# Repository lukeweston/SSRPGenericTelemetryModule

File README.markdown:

- Micro-SD card for removable datalogging and storage   
- Real-time clock with battery backup   
- USB interface for battery recharging as well as PC-based communications, programming, debugging or data analysis   
- Barometric pressure sensor (30,000 feet approx. maximum)   
- 3-axis MEMS gyroscope   
- 3-axis accelerometer   
- 3-axis magnetometer   
- Single-axis high-range accelerometer (up to 200 g-units) for rocket motor characterisation   
- Differential pressre transducer for pitot tube airspeed measurement   
- Temperature sensor   
- Central microcontroller (Atmel ATmega2561)   
- On-board Silicon Labs Si1000 microcontroller with integrated UHF transceiver (100mW transmit power)   
- Power supply from a single 3.7V lithium-polymer cell, with on-board recharge control   
- 8 channels of 0-4096mV analog data acquisition from additional external payload electronics.   
- Support for a range of different GPS receiver modules and different antenna types, mounted away from the main board to provide more flexible antenna mounting.   
- Support for a range of different external RF telemetry hardware if more performance is desired than the on-board Si1000 can provide.   
- For example, the RFDesign RFD900 900 MHz RF modem can be used, which consists of a Si1000 microcontroller with external RF LNA and PA, providing telemetry ranges of up to
nearly 100 kilometers with line-of-sight.

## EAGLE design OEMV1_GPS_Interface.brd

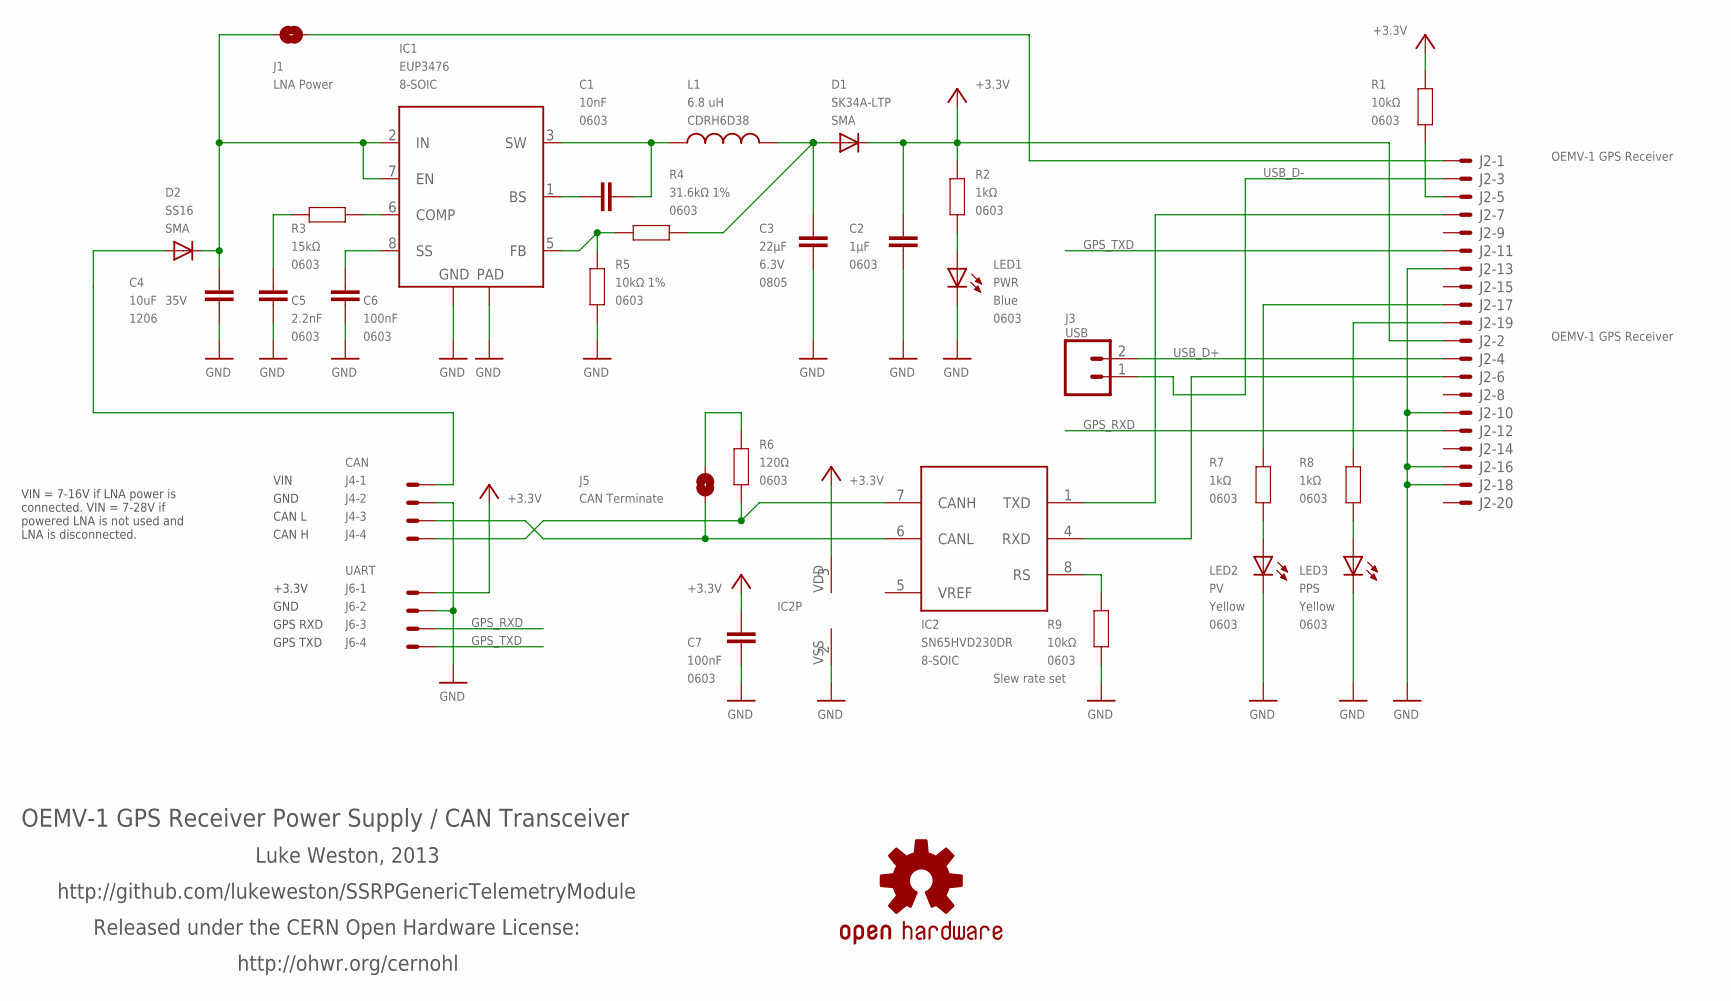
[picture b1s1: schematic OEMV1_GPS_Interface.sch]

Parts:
C1: 10nF; 0603
C2: 1µF; 0603
C3: 22µF; 0805; VOLTAGE 6.3V
C4: 10uF; C1206; VOLTAGE 35V
C5: 2.2nF; 0603
C6, C7: 100nF; 0603
D1: SK34A-LTP; SMA-DIODE
D2: SS16; SMA-DIODE
IC1: EUP3476; SO08T
IC2: SN65HVD230DR; SO-08
J1: LNA Power; SJ
J2: OEMV-1 GPS Receiver; 87758-2016
J3: USB; 1X02
J4: CAN; 22-23-2041
J5: CAN Terminate; SJ
J6: UART; 22-23-2041
L1: 6.8 uH; CDRH
LED1: PWR; LED-0603
LED2: PV; LED-0603
LED3: PPS; LED-0603
R1, R9: 10kΩ; 0603
R2, R7, R8: 1kΩ; 0603
R3: 15kΩ; 0603
R4: 31.6kΩ 1%; 0603
R5: 10kΩ 1%; 0603
R6: 120Ω; 0603
SY: OSHW-LOGOS; OSHW-LOGO-S

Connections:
!RESET: J2.5, R1.2
+3.3V: C2.2, C7.2, D1.C, IC2.3 (VDD), J2.2, J6.1, R1.1, R2.1
CANH: IC2.7 (CANH), J4.4, R6.1
CANL: IC2.6 (CANL), J4.3, J5.2
GND: C2.1, C3.2, C4.2, C5.1, C6.1, C7.1, IC1.4 (GND), IC1.9 (TGND), IC2.2 (VSS), J2.10, J2.13, J2.16, J2.18, J4.2, J6.2, LED1.C, LED2.C, LED3.C, R5.2, R9.2
GPS_CAN_RX: IC2.4 (RXD), J2.6
GPS_CAN_TX: IC2.1 (TXD), J2.7
GPS_RXD: J2.12, J6.3
GPS_TXD: J2.11, J6.4
unnamed: LED2.A, R7.1
unnamed: LED3.A, R8.1
unnamed: C1.2, IC1.1 (BS)
unnamed: D2.A, J4.1
unnamed: J5.1, R6.2
unnamed: C5.2, R3.2
unnamed: C3.1, D1.A, L1.2, R4.2
unnamed: LED1.A, R2.2
unnamed: C4.1, D2.C, IC1.2 (IN), IC1.7 (EN), J1.1
unnamed: C1.1, IC1.3 (SW), L1.1
unnamed: IC1.6 (COMP), R3.1
unnamed: C6.2, IC1.8 (SS)
unnamed: IC1.5 (FB), R4.1, R5.1
unnamed: IC2.8 (RS), R9.1
PPS_OUT: J2.19, R8.2
PV_OUT: J2.17, R7.2
USB_D+: J2.4, J3.2
USB_D-: J2.3, J3.1
VIN: J1.2, J2.1
VREF: IC2.5 (VREF)

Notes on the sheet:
OEMV-1 GPS Receiver Power Supply / CAN Transceiver
Luke Weston, 2013
http://github.com/lukeweston/SSRPGenericTelemetryModule
Released under the CERN Open Hardware License:
http://ohwr.org/cernohl
VIN
GND
CAN L
CAN H
+3.3V
GPS RXD
GPS TXD
VIN = 7-16V if LNA power is connected. VIN = 7-28V if powered LNA is not used and LNA is disconnected.

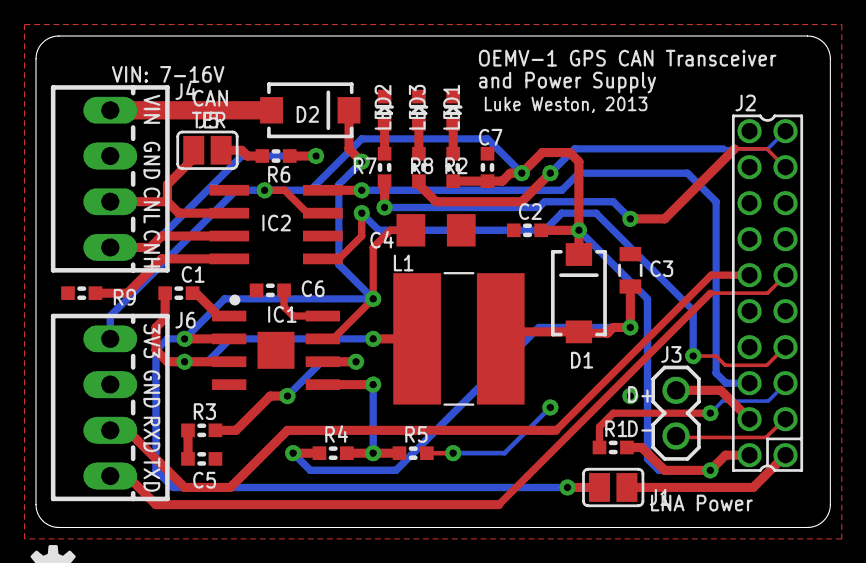
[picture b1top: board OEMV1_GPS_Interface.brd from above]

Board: 2 copper layers, 44.1 x 27.3 mm, 31 parts (0 on the bottom side), 28 nets.

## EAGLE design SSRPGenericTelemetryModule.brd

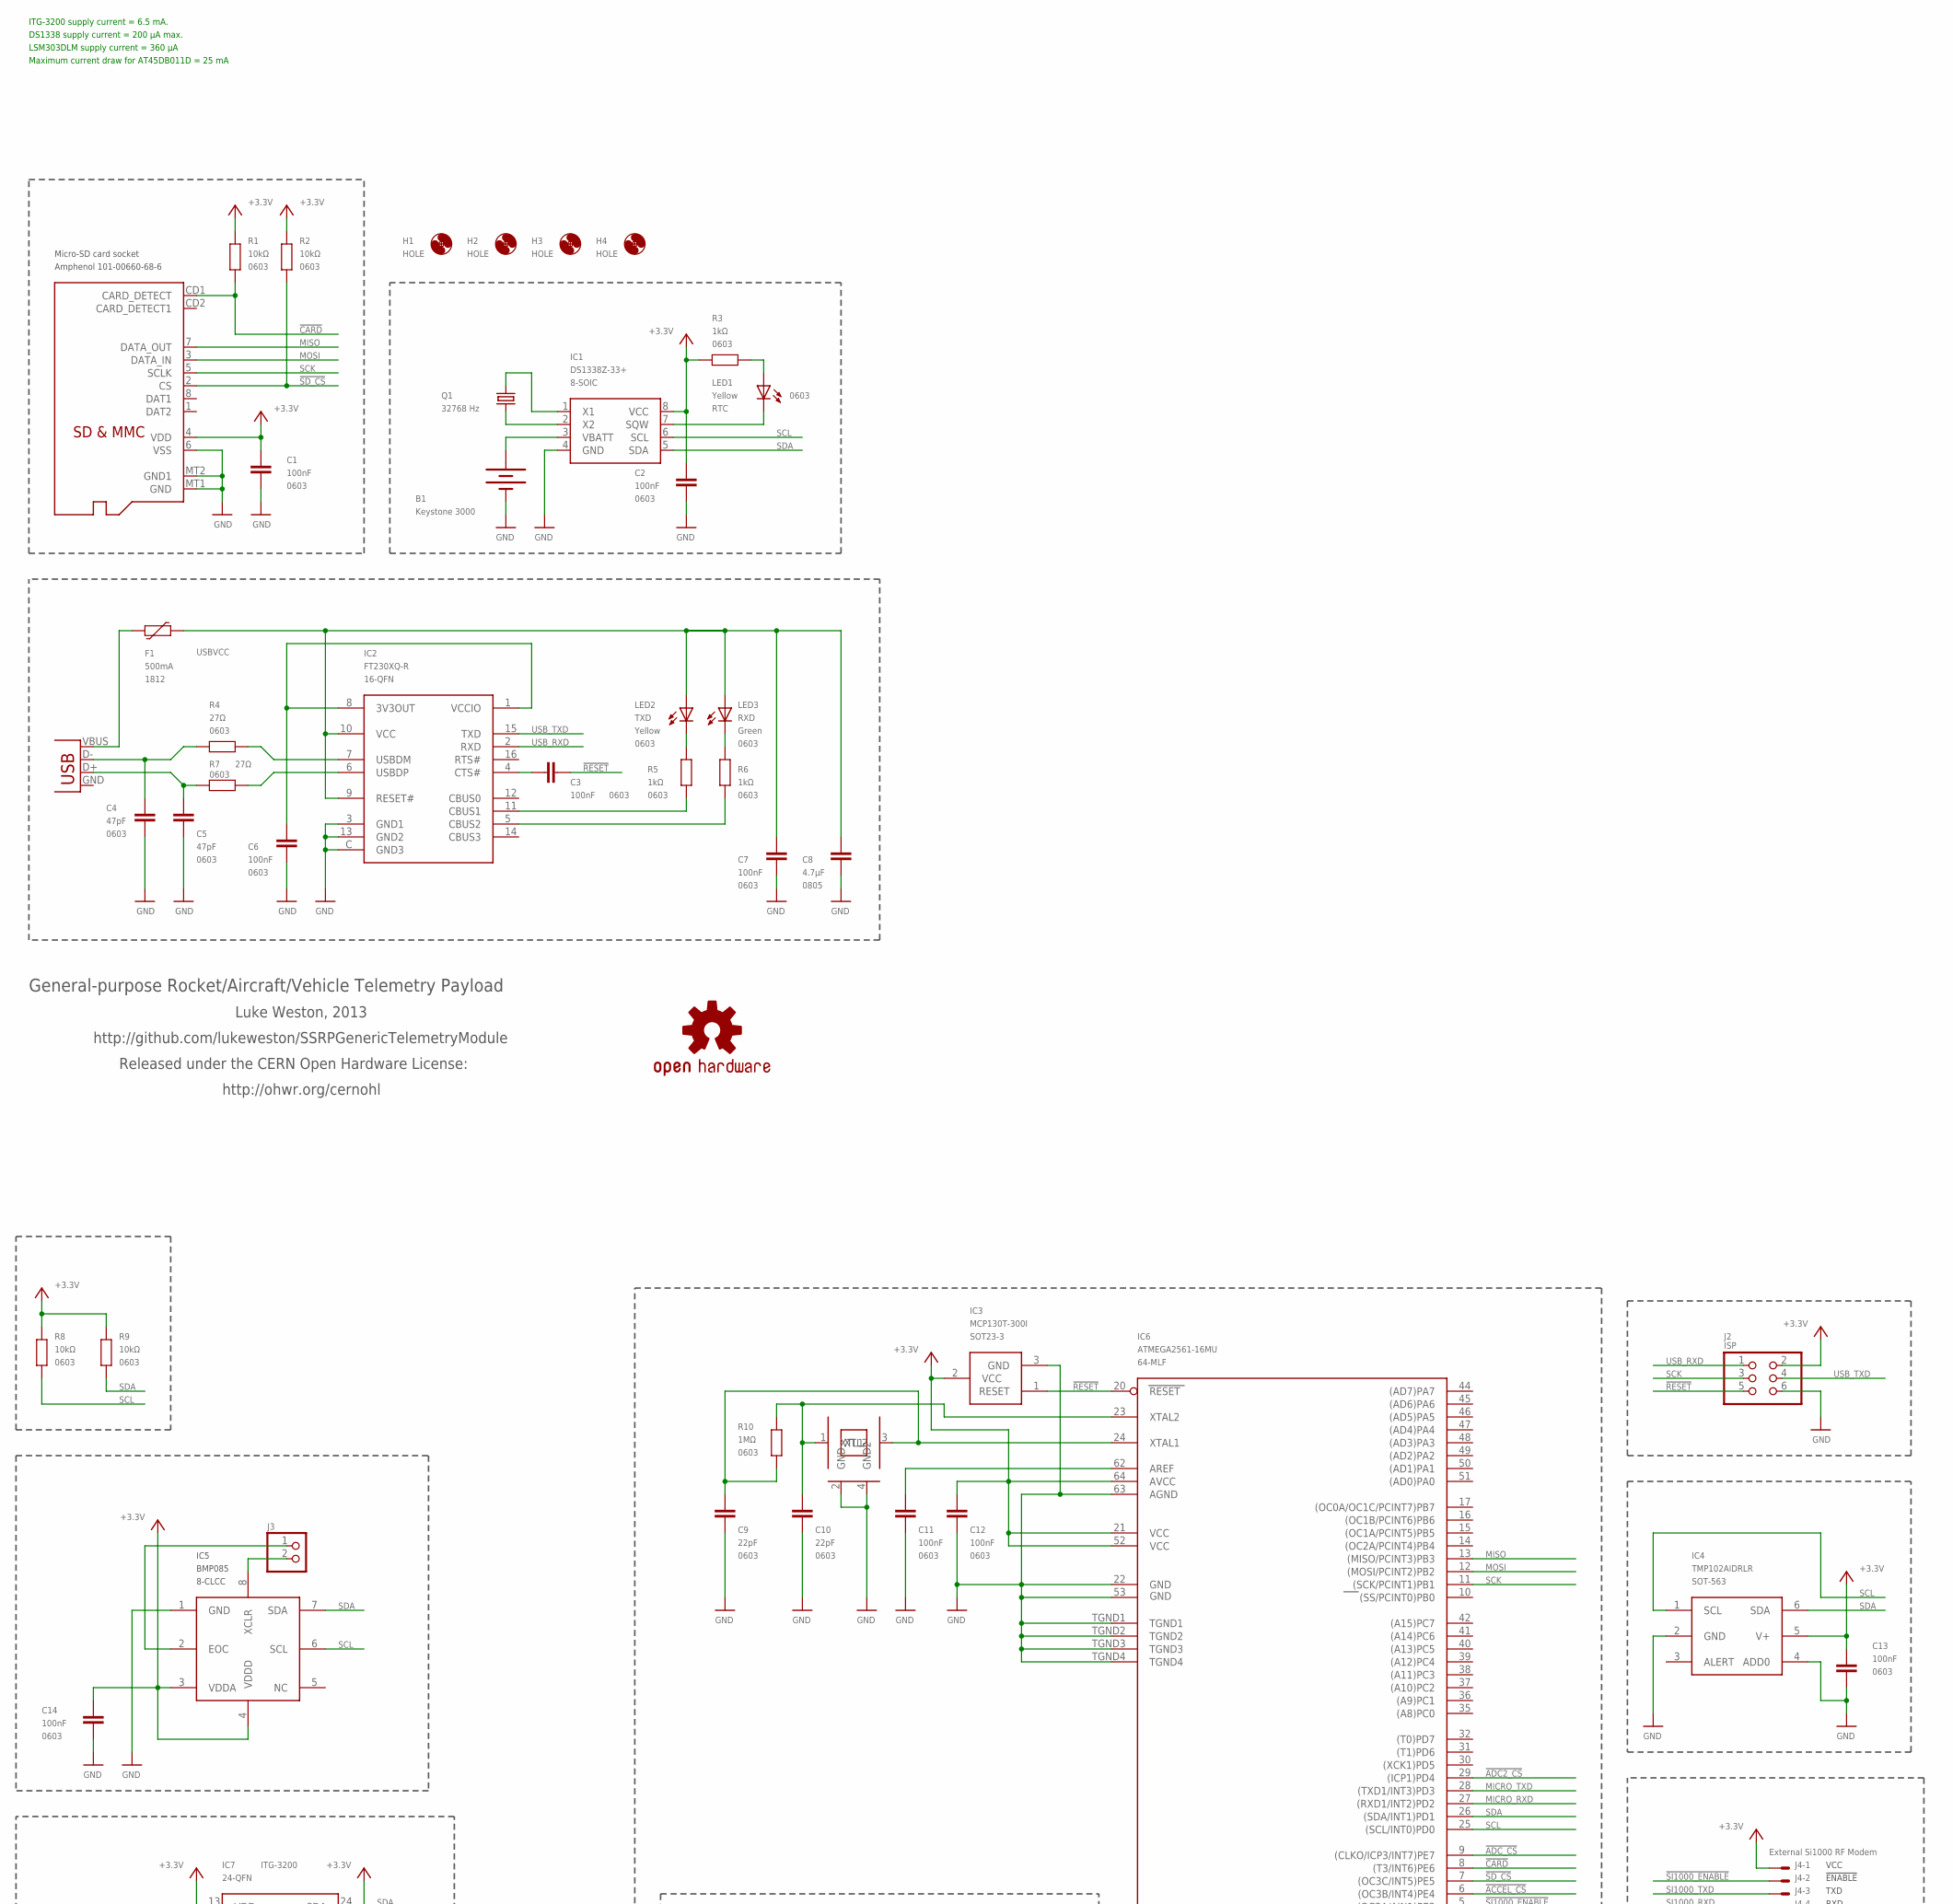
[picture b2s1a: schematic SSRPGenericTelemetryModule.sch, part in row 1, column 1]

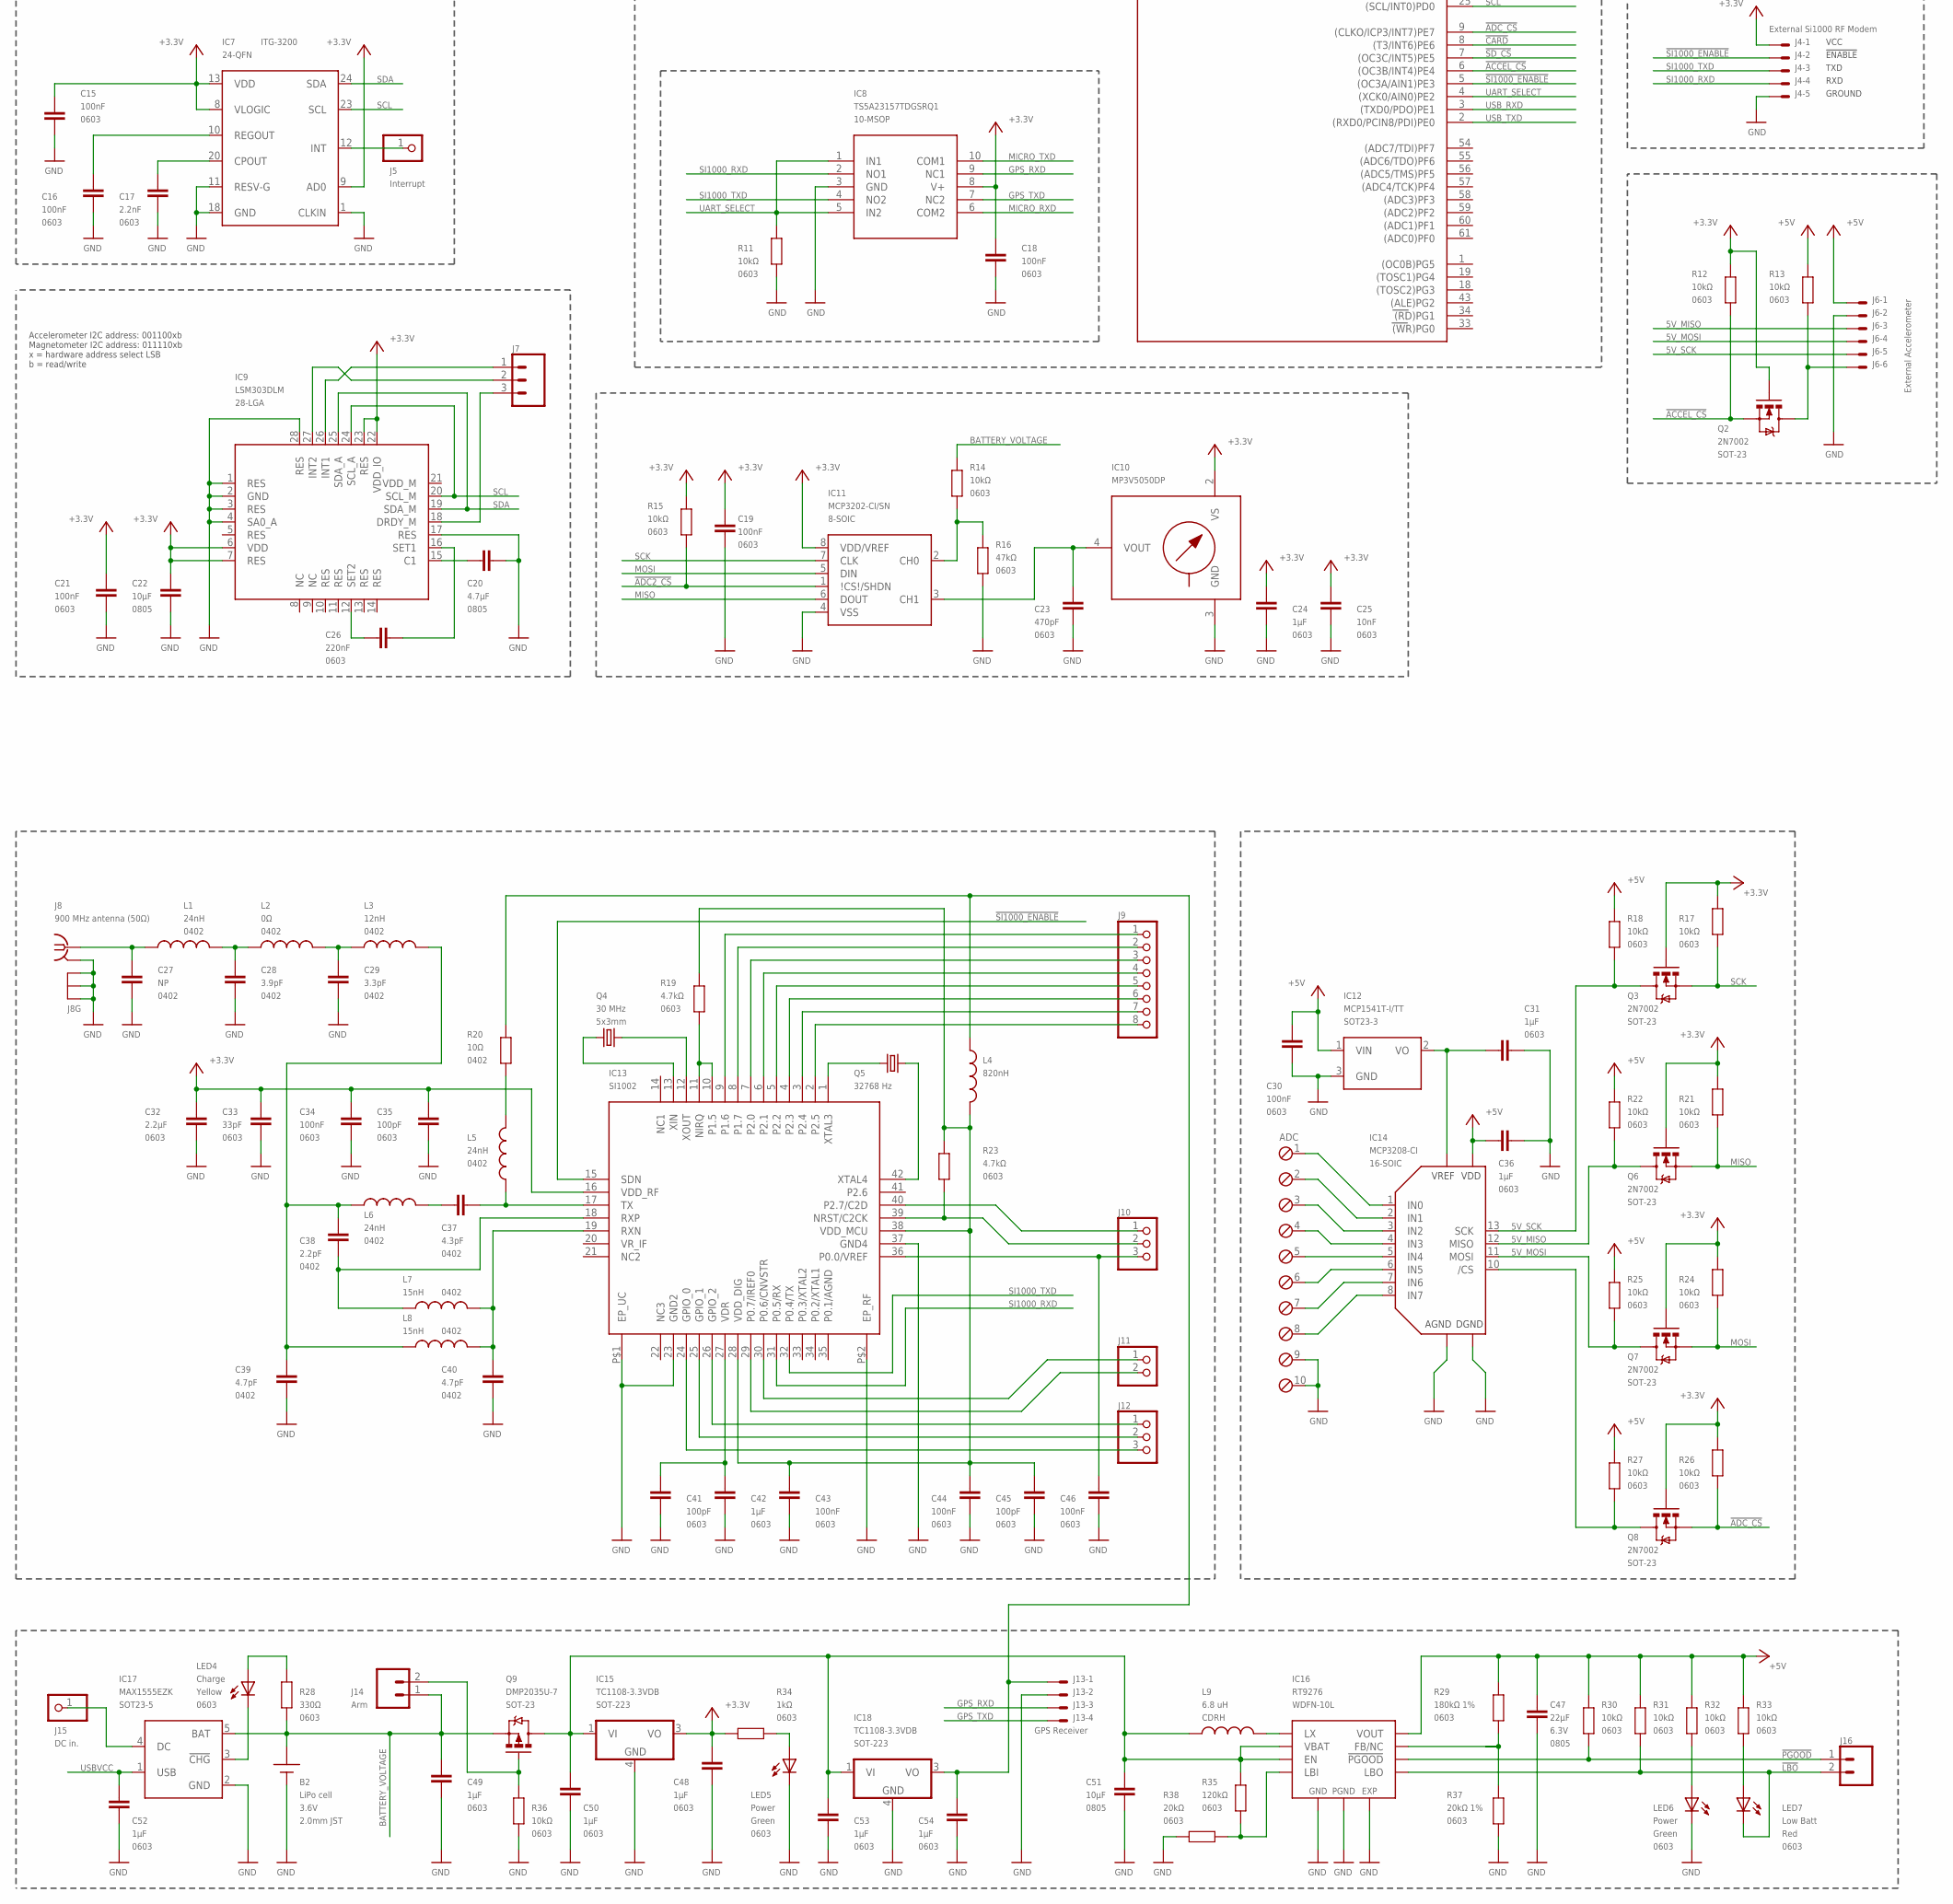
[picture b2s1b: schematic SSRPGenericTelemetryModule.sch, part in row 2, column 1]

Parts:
B1: Keystone 3000; BATTCON_12MM
B2: LiPo cell; JST-2MM-TH-RA; VOLTAGE 3.6V
C1, C2, C3, C6, C7, C11, C12, C13, C14, C15, C16, C18, C19, C21, C30, C34, C43, C44, C46: 100nF; 0603
C4, C5: 47pF; 0603
C8, C20: 4.7µF; 0805
C9, C10: 22pF; 0603
C17: 2.2nF; 0603
C22, C51: 10µF; 0805
C23: 470pF; 0603
C24, C31, C36, C42, C48, C49, C50, C52, C53, C54: 1µF; 0603
C25: 10nF; 0603
C26: 220nF; 0603
C27: NP; C0402
C28: 3.9pF; C0402
C29: 3.3pF; C0402
C32: 2.2µF; 0603
C33: 33pF; 0603
C35, C41, C45: 100pF; 0603
C37: 4.3pF; C0402
C38: 2.2pF; C0402
C39, C40: 4.7pF; C0402
C47: 22µF; 0805; VOLTAGE 6.3V
F1: 500mA; 1812
H1, H2, H3, H4: HOLE; 3,2
IC1: DS1338Z-33+; SO08@1
IC2: FT230XQ-R; QFN4X4-16
IC3: MCP130T-300I; SOT23-3
IC4: TMP102AIDRLR; SOT563
IC5: BMP085
IC6: ATMEGA2561-16MU; MLF64
IC7: ITG-3200; QFN-24
IC8: TS5A23157TDGSRQ1; MSOP10
IC9: LSM303DLM; LGA28-5X5
IC10: MP3V5050DP; 1351
IC11: MCP3202-CI/SN; SO-08
IC12: MCP1541T-I/TT; SOT23
IC13: SI1002; QFN42_MCM
IC14: MCP3208-CI; SOIC16
IC15, IC18: TC1108-3.3VDB; SOT223
IC16: RT9276; WDFN-10L-3X3
IC17: MAX1555EZK; SOT23-5L
J1: MicroSD Card; ADAFRUIT_MICROSD
J2: ISP; 2X03PTH
J3, J11: PINHD-1X2; 1X02
J4: External Si1000 RF Modem; 22-23-2051
J5: Interrupt; 1X01
J6: External Accelerometer; 7395-06
J7: M03PTH; 1X03
J8: 900 MHz antenna (50Ω); J502-ND-142-0701-801/806
J9: PINHD-1X8; 1X08
J10, J12: PINHD-1X3; 1X03
J13: GPS Receiver; 7395-04
J14: Arm; 1X02
J15: DC in.; 1X01
J16: Status; 1X02
L1, L5, L6: 24nH; C0402
L2: 0Ω; C0402
L3: 12nH; C0402
L4: 820nH; C0402
L7, L8: 15nH; C0402
L9: 6.8 uH; CDRH
LED1: RTC; LED-0603
LED2: TXD; LED-0603
LED3: RXD; LED-0603
LED4: Charge; LED-0603
LED5, LED6: Power; LED-0603
LED7: Low Batt; LED-0603
Q1, Q5: 32768 Hz; SMD3215_XTAL
Q2, Q3, Q6, Q7, Q8: 2N7002; SOT23-3
Q4: 30 MHz; CRYSTAL-SMD-5X3
Q9: DMP2035U-7; SOT23-3
R1, R2, R8, R9, R11, R12, R13, R14, R15, R17, R18, R21, R22, R24, R25, R26, R27, R30, R31, R32, R33, R36: 10kΩ; 0603
R3, R5, R6, R34: 1kΩ; 0603
R4, R7: 27Ω; 0603
R10: 1MΩ; 0603
R16: 47kΩ; 0603
R19, R23: 4.7kΩ; 0603
R20: 10Ω; C0402
R28: 330Ω; 0603
R29: 180kΩ 1%; 0603
R35: 120kΩ; 0603
R37: 20kΩ 1%; 0603
R38: 20kΩ; 0603
SY: OSHW-LOGOS; OSHW-LOGO-S
X1: USB-MICROB
X2: ADC; 10POL254
XTL1: SMD3225-16MHZ 3.2 x 2.5mm crystal; CRYSTAL-SMD-3X2

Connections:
5V_MISO: IC14.12 (MISO), J6.3, Q6.3 (D), R22.1
5V_MOSI: IC14.11 (MOSI), J6.4, Q7.3 (D), R25.1
5V_SCK: IC14.13 (SCK), J6.5, Q3.3 (D), R18.1
!ACCEL_CS: IC6.6 ((OC3B/INT4)PE4), Q2.2 (S), R12.1
!ADC2_CS: IC6.29 ((ICP1)PD4), IC11.1 (\!CS\!/SHDN), R15.1
!ADC_CS: IC6.9 ((CLKO/ICP3/INT7)PE7), Q8.2 (S), R26.1
!ADC_CS_5V: IC14.10 (/CS), Q8.3 (D), R27.1
!CARD: IC6.8 ((T3/INT6)PE6), J1.CD1 (CARD_DETECT), R1.2
!LBO: IC16.4 (LBO), J16.2, LED7.C, R31.1
!PGOOD: IC16.8 (!PGOOD), J16.1, R30.1
!RESET: C3.2, IC3.1 (RESET), IC6.20 (RESET), J2.5
!SD_CS: IC6.7 ((OC3C/INT5)PE5), J1.2 (CS), R2.2
!SI1000_ENABLE: IC6.5 ((OC3A/AIN1)PE3), IC13.15 (SDN), J4.2
+3V3: C1.1, C2.1, C12.1, C13.1, C14.1, C15.1, C18.2, C19.1, C21.2, C22.2, C24.1, C25.1, C32.2, C33.2, C34.2, C35.2, C48.1, IC1.8 (VCC), IC3.2 (VCC), IC4.5 (V+), IC5.3 (VDDA), IC5.4 (VDDD), IC6.21 (VCC), IC6.52 (VCC1), IC6.64 (AVCC), IC7.8 (VLOGIC), IC7.9 (AD0), IC7.13 (VDD), IC8.8 (V+), IC9.6 (VDD), IC9.7 (RES), IC9.22 (VDD_IO), IC9.23 (RES), IC10.2 (VS), IC11.8 (VDD/VREF), IC13.16 (VDD_RF), IC15.3 (VO), J1.4 (VDD), J2.2, J4.1, Q2.1 (G), Q3.1 (G), Q6.1 (G), Q7.1 (G), Q8.1 (G), R1.1, R2.1, R3.2, R8.2, R9.2, R12.2, R15.2, R17.2, R21.2, R24.2, R26.2, R34.2
+5V: C30.2, C36.1, C47.1, IC12.1 (VIN), IC14.16 (VDD), IC16.2 (VOUT), J6.1, R13.2, R18.2, R22.2, R25.2, R27.2, R29.2, R30.2, R31.2, R32.2, R33.2
ANALOG_BAROMETER: C23.1, IC10.4 (VOUT), IC11.3 (CH1)
BATTERY_VOLTAGE: B2.+, C49.1, IC17.5 (BAT), J14.1, Q9.2 (S), R14.2, R28.1
FB1: IC16.3 (FB/NC), R29.1, R37.2
GND: B1.GND (-), B2.-, C1.2, C2.2, C4.2, C5.2, C6.2, C7.2, C8.2, C9.2, C10.2, C11.2, C12.2, C13.2, C14.2, C15.2, C16.2, C17.2, C18.1, C19.2, C20.2, C21.1, C22.1, C23.2, C24.2, C25.2, C27.2, C28.2, C29.2, C30.1, C31.2, C32.1, C33.1, C34.1, C35.1, C36.2, C39.2, C40.2, C41.1, C42.1, C43.1, C44.1, C45.1, C46.1, C47.2, C48.2, C49.2, C50.2, C51.2, C52.2, C53.2, C54.2, IC1.4 (GND), IC2.3 (GND1), IC2.13 (GND2), IC2.C (GND3), IC3.3 (GND), IC4.2 (GND), IC4.4 (ADD0), IC5.1 (GND), IC6.22 (GND), IC6.53 (GND1), IC6.63 (AGND), IC6.TGND1, IC6.TGND2, IC6.TGND3, IC6.TGND4, IC7.1 (CLKIN), IC7.11 (RESV-G), IC7.18 (GND), IC8.3 (GND), IC9.1 (RES), IC9.2 (GND), IC9.3 (RES), IC9.4 (SA0_A), IC9.17 (RES), IC9.28 (RES), IC10.3 (GND), IC11.4 (VSS), IC12.3 (GND), IC13.23 (GND2), IC13.37 (GND4), IC13.EP1 (GND5), IC13.EP2 (GND6), IC13.EP3 (GND7), IC13.EP4 (GND8), IC13.EP5 (GND9), IC13.EP6 (GND10), IC13.EP7 (GND11), IC13.EP8 (GND12), IC13.P$1 (EP_UC), IC13.P$2 (EP_RF), IC14.9 (DGND), IC14.14 (AGND), IC15.4 (GND), IC16.5 (GND), IC16.10 (PGND), IC16.EXP, IC17.2 (GND), IC18.4 (GND), J1.6 (VSS), J1.MT1 (GND), J1.MT2 (GND1), J2.6, J4.5, J6.2, J8.G@1 (GND), J8.G@2 (GND), J8.G@3 (GND), J8.G@4 (GND), J13.2, LED5.C, LED6.C, R11.1, R16.1, R36.1, R37.1, R38.1, X2.9, X2.10, XTL1.2 (GND), XTL1.4 (GND2)
GPS_RXD: IC8.9 (NC1), J13.3
GPS_TXD: IC8.7 (NC2), J13.4
LBI1: IC16.7 (LBI), R35.1, R38.2
LX1: IC16.9 (LX), L9.2
MICRO_RXD: IC6.27 ((RXD1/INT2)PD2), IC8.6 (COM2)
MICRO_TXD: IC6.28 ((TXD1/INT3)PD3), IC8.10 (COM1)
MISO: IC6.13 ((MISO/PCINT3)PB3), IC11.6 (DOUT), J1.7 (DATA_OUT), Q6.2 (S), R21.1
MOSI: IC6.12 ((MOSI/PCINT2)PB2), IC11.5 (DIN), J1.3 (DATA_IN), Q7.2 (S), R24.1
unnamed: J6.6, Q2.3 (D), R13.1
unnamed: C43.2, C44.2, C45.2, IC13.28 (VDD_DIG), IC13.38 (VDD_MCU), L4.1, R19.2, R23.2
unnamed: C38.2, IC13.18 (RXP), L7.2
unnamed: IC13.40 (P2.7/C2D), J10.1
unnamed: IC9.18 (DRDY_M), J7.3
unnamed: C27.1, J8.1, L1.1
unnamed: IC13.1 (XTAL3), Q5.X2 (2)
unnamed: IC13.42 (XTAL4), Q5.X1 (1)
unnamed: IC13.30 (P0.6/CNVSTR), J11.1
unnamed: IC9.27 (INT2), J7.2
unnamed: C11.1, IC6.62 (AREF)
unnamed: IC1.2 (X2), Q1.X2 (2)
unnamed: B1.PWR@1 (+), IC1.3 (VBATT)
unnamed: IC1.1 (X1), Q1.X1 (1)
unnamed: IC1.7 (SQW), LED1.C
unnamed: IC9.26 (INT1), J7.1
unnamed: C26.1, IC9.12 (SET2)
unnamed: C26.2, IC9.16 (SET1)
unnamed: C10.1, IC6.23 (XTAL2), R10.1, XTL1.1 (XTL1)
unnamed: C20.1, IC9.15 (C1)
unnamed: IC13.29 (P0.7/IREF0), J11.2
unnamed: IC7.12 (INT), J5.1
unnamed: C9.1, IC6.24 (XTAL1), R10.2, XTL1.3 (XTL2)
unnamed: LED1.A, R3.1
unnamed: C16.1, IC7.10 (REGOUT)
unnamed: LED2.C, R5.2
unnamed: C17.1, IC7.20 (CPOUT)
unnamed: C54.1, IC18.3 (VO), J13.1, L4.2, R20.2
unnamed: IC14.8 (IN7), X2.8
unnamed: IC14.7 (IN6), X2.7
unnamed: LED3.C, R6.2
unnamed: C6.1, IC2.1 (VCCIO), IC2.8 (3V3OUT)
unnamed: IC5.8 (XCLR), J3.2
unnamed: IC5.2 (EOC), J3.1
unnamed: IC11.2 (CH0), R14.1, R16.2
unnamed: IC14.6 (IN5), X2.6
unnamed: IC14.5 (IN4), X2.5
unnamed: IC14.4 (IN3), X2.4
unnamed: IC14.3 (IN2), X2.3
unnamed: IC14.2 (IN1), X2.2
unnamed: IC14.1 (IN0), X2.1
unnamed: IC2.7 (USBDM), R4.2
unnamed: C31.1, IC12.2 (VO), IC14.15 (VREF)
unnamed: LED6.A, R32.1
unnamed: IC2.6 (USBDP), R7.2
unnamed: C5.1, R7.1, X1.D+
unnamed: C4.1, R4.1, X1.D-
unnamed: F1.1, X1.VBUS
unnamed: IC2.11 (CBUS1), R5.1
unnamed: IC2.5 (CBUS2), R6.1
unnamed: C3.1, IC2.4 (CTS#)
unnamed: LED7.A, R33.1
unnamed: IC13.24 (GPIO_0), J12.3
unnamed: IC13.25 (GPIO_1), J12.2
unnamed: IC13.26 (GPIO_2), J12.1
unnamed: C41.2, C42.2, IC13.27 (VDR)
unnamed: C46.2, IC13.36 (P0.0/VREF), J10.3
unnamed: J14.2, Q9.1 (G), R36.2
unnamed: IC17.3 (!CHG), LED4.C
unnamed: LED4.A, R28.2
unnamed: IC17.4 (DC), J15.1
unnamed: LED5.A, R34.1
unnamed: IC13.39 (NRST/C2CK), J10.2, R23.1
unnamed: IC13.2 (P2.5), J9.8
unnamed: IC13.3 (P2.4), J9.7
unnamed: IC13.4 (P2.3), J9.6
unnamed: IC13.5 (P2.2), J9.5
unnamed: IC13.6 (P2.1), J9.4
unnamed: IC13.7 (P2.0), J9.3
unnamed: IC13.8 (P1.7), J9.2
unnamed: IC13.9 (P1.6), J9.1
unnamed: IC13.10 (P1.5), IC13.11 (NIRQ), R19.1
unnamed: IC13.12 (XOUT), Q4.3 (2)
unnamed: IC13.13 (XIN), Q4.1
unnamed: C37.1, IC13.17 (TX), L5.1
unnamed: C37.2, L6.2
unnamed: C40.1, IC13.19 (RXN), L7.1, L8.1
unnamed: L5.2, R20.1
unnamed: C28.1, L1.2, L2.1
unnamed: C29.1, L2.2, L3.1
unnamed: C38.1, C39.1, L3.2, L6.1, L8.2
SCK: IC6.11 ((SCK/PCINT1)PB1), IC11.7 (CLK), J1.5 (SCLK), J2.3, Q3.2 (S), R17.1
SCL: IC1.6 (SCL), IC4.1 (SCL), IC5.6 (SCL), IC6.25 ((SCL/INT0)PD0), IC7.23 (SCL), IC9.20 (SCL_M), IC9.24 (SCL_A), R8.1
SDA: IC1.5 (SDA), IC4.6 (SDA), IC5.7 (SDA), IC6.26 ((SDA/INT1)PD1), IC7.24 (SDA), IC9.19 (SDA_M), IC9.25 (SDA_A), R9.1
SI1000_RXD: IC8.2 (NO1), IC13.31 (P0.5/RX), J4.4
SI1000_TXD: IC8.4 (NO2), IC13.32 (P0.4/TX), J4.3
UART_SELECT: IC6.4 ((XCK0/AIN0)PE2), IC8.1 (IN1), IC8.5 (IN2), R11.2
USBVCC: C7.1, C8.1, C52.1, F1.2, IC2.9 (RESET#), IC2.10 (VCC), IC17.1 (USB), LED2.A, LED3.A
USB_RXD: IC2.2 (RXD), IC6.3 ((TXD0/PDO)PE1), J2.1
USB_TXD: IC2.15 (TXD), IC6.2 ((RXD0/PCIN8/PDI)PE0), J2.4
VR_IF: IC13.20 (VR_IF)
V_BATT: C50.1, C51.1, C53.1, IC15.1 (VI), IC16.1 (EN), IC16.6 (VBAT), IC18.1 (VI), L9.1, Q9.3 (D), R35.2

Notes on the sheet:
Accelerometer I2C address: 001100xb Magnetometer I2C address: 011110xb x = hardware address select LSB b = read/write
LSM303DLM supply current = 360 µA
DS1338 supply current = 200 µA max.
ITG-3200 supply current = 6.5 mA.
Maximum current draw for AT45DB011D = 25 mA
VCC
!ENABLE
TXD
RXD
GROUND
Micro-SD card socket
Amphenol 101-00660-68-6
FT230XQ-R
General-purpose Rocket/Aircraft/Vehicle Telemetry Payload
Luke Weston, 2013
http://github.com/lukeweston/SSRPGenericTelemetryModule
Released under the CERN Open Hardware License:
http://ohwr.org/cernohl
8-CLCC
BMP085
IC5

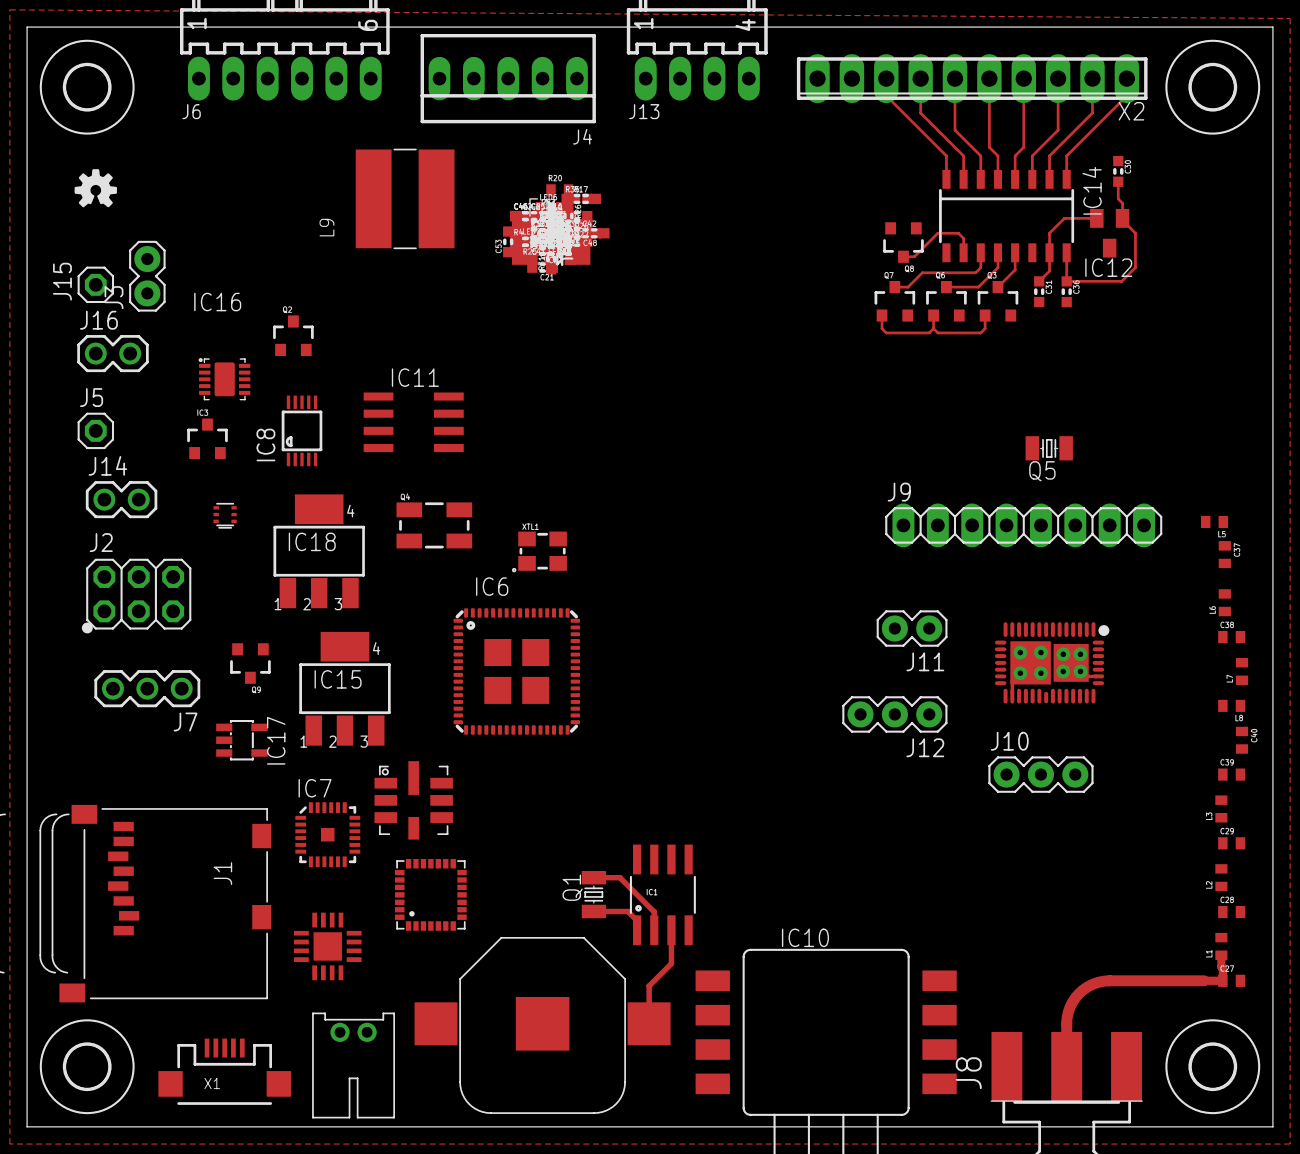
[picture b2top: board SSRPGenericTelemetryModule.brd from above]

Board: 2 copper layers, 92.1 x 81.3 mm, 162 parts (0 on the bottom side), 118 nets.

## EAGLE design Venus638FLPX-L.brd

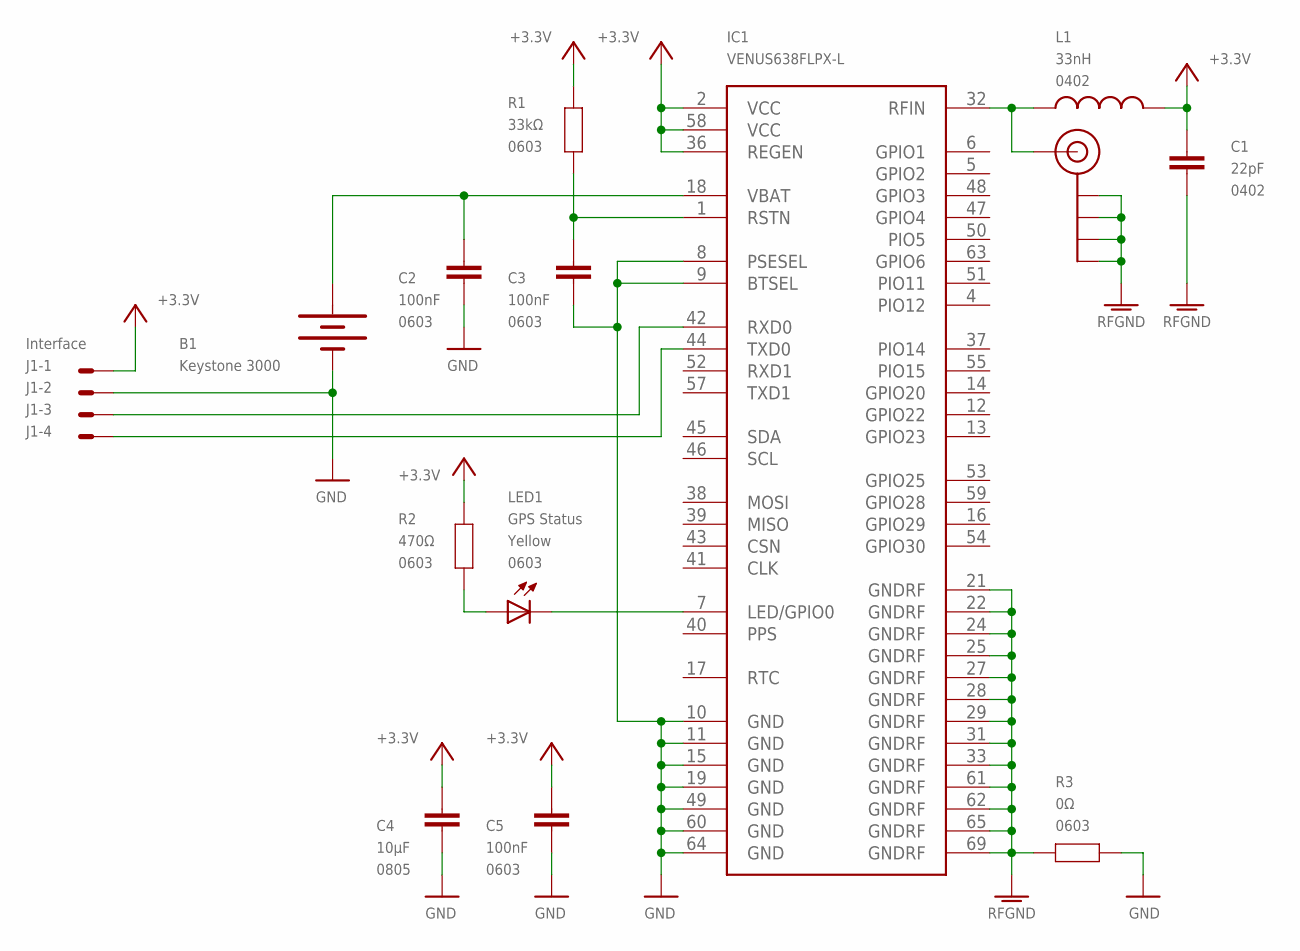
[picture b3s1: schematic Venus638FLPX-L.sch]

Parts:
B1: Keystone 3000; BATTCON_12MM
C1: 22pF; C0402
C2, C3, C5: 100nF; 0603
C4: 10µF; 0805
IC1: VENUS638FLPX-L; VENUS638FLPX
J1: Interface; 7395-04
JP1: Antenna; SMA-EDGE
L1: 33nH; C0402
LED1: GPS Status; LED-0603
R1: 33kΩ; 0603
R2: 470Ω; 0603
R3: 0Ω; 0603

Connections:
+3.3V: C1.2, C4.2, C5.2, IC1.2 (VCC), IC1.36 (REGEN), IC1.58 (VCC), J1.1, L1.1, R1.1, R2.1
ANT2: IC1.32 (RFIN), JP1.SIG (SIGNAL), L1.2
GND: B1.GND (-), C2.1, C3.1, C4.1, C5.1, IC1.8 (PSESEL), IC1.9 (BTSEL), IC1.10 (GND), IC1.11 (GND), IC1.15 (GND), IC1.19 (GND), IC1.49 (GND), IC1.60 (GND), IC1.64 (GND), J1.2, R3.1
unnamed: C3.2, IC1.1 (RSTN), R1.2
unnamed: B1.PWR@1 (+), C2.2, IC1.18 (VBAT)
unnamed: IC1.7 (LED/GPIO0), LED1.C
unnamed: LED1.A, R2.2
RFGND: C1.1, IC1.21 (GNDRF), IC1.22 (GNDRF), IC1.24 (GNDRF), IC1.25 (GNDRF), IC1.27 (GNDRF), IC1.28 (GNDRF), IC1.29 (GNDRF), IC1.31 (GNDRF), IC1.33 (GNDRF), IC1.61 (GNDRF), IC1.62 (GNDRF), IC1.65 (GNDRF), IC1.69 (GNDRF), JP1.GND@0 (GND), JP1.GND@1 (GND), JP1.GND@2 (GND), JP1.GND@3 (GND), R3.2
RXD: IC1.42 (RXD0), J1.3
TXD: IC1.44 (TXD0), J1.4

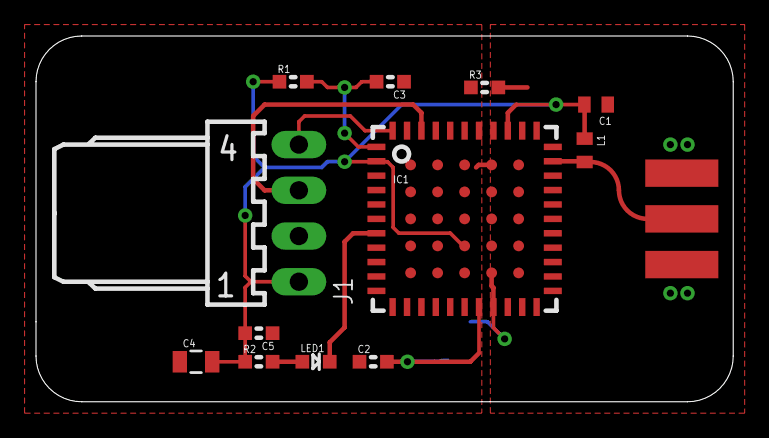
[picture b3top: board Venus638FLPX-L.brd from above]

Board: 2 copper layers, 38.7 x 20.3 mm, 14 parts (1 on the bottom side), 10 nets.
